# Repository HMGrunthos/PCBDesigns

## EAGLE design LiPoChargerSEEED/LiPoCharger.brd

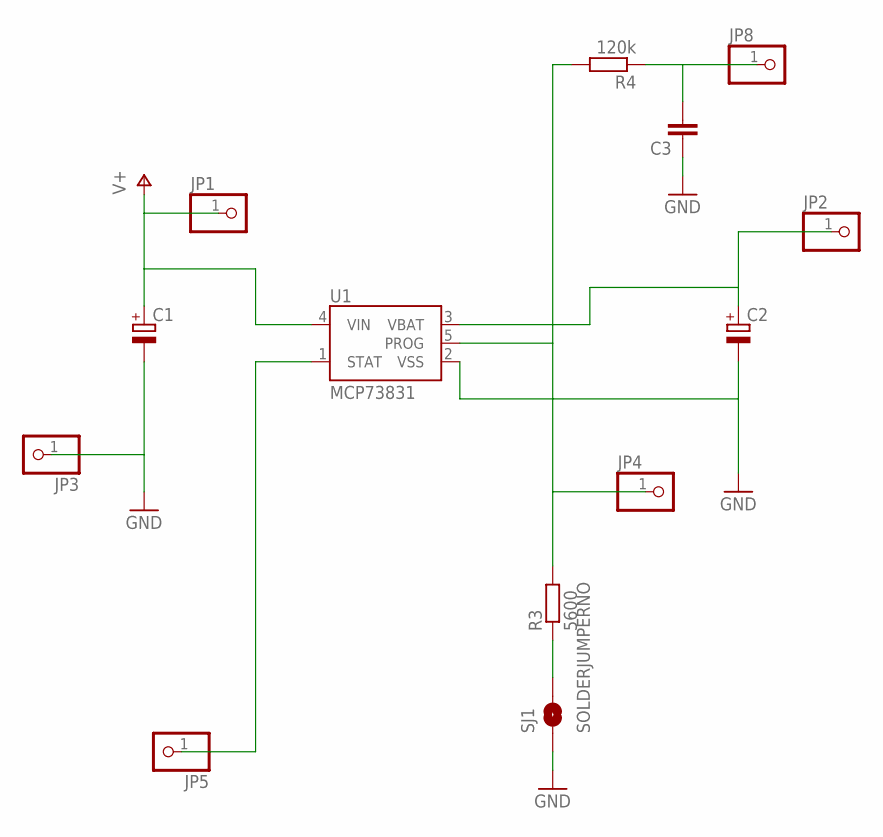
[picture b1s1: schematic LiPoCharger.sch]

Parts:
C1, C2: CPOL-EUE2.5-6; E2,5-6
C3: C-EUC1206; C1206
JP1, JP2, JP3, JP4, JP5, JP8: PINHD-1X1; 1X01
R3: 5600; R0402
R4: 120k; R0402
SJ1: SOLDERJUMPERNO; SJ_2S-NO
U1: MCP73831; SOT23-5

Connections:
GND: C1.-, C2.-, C3.1, JP3.1, SJ1.1, U1.2 (VSS)
unnamed: JP5.1, U1.1 (STAT)
unnamed: JP4.1, R3.2, R4.2, U1.5 (PROG)
unnamed: C3.2, JP8.1, R4.1
unnamed: R3.1, SJ1.2
V+: C1.+, JP1.1, U1.4 (VIN)
VBATT: C2.+, JP2.1, U1.3 (VBAT)

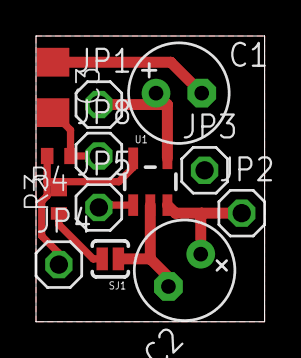
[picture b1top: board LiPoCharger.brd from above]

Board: 2 copper layers, 12.7 x 15.9 mm, 13 parts (0 on the bottom side), 7 nets.

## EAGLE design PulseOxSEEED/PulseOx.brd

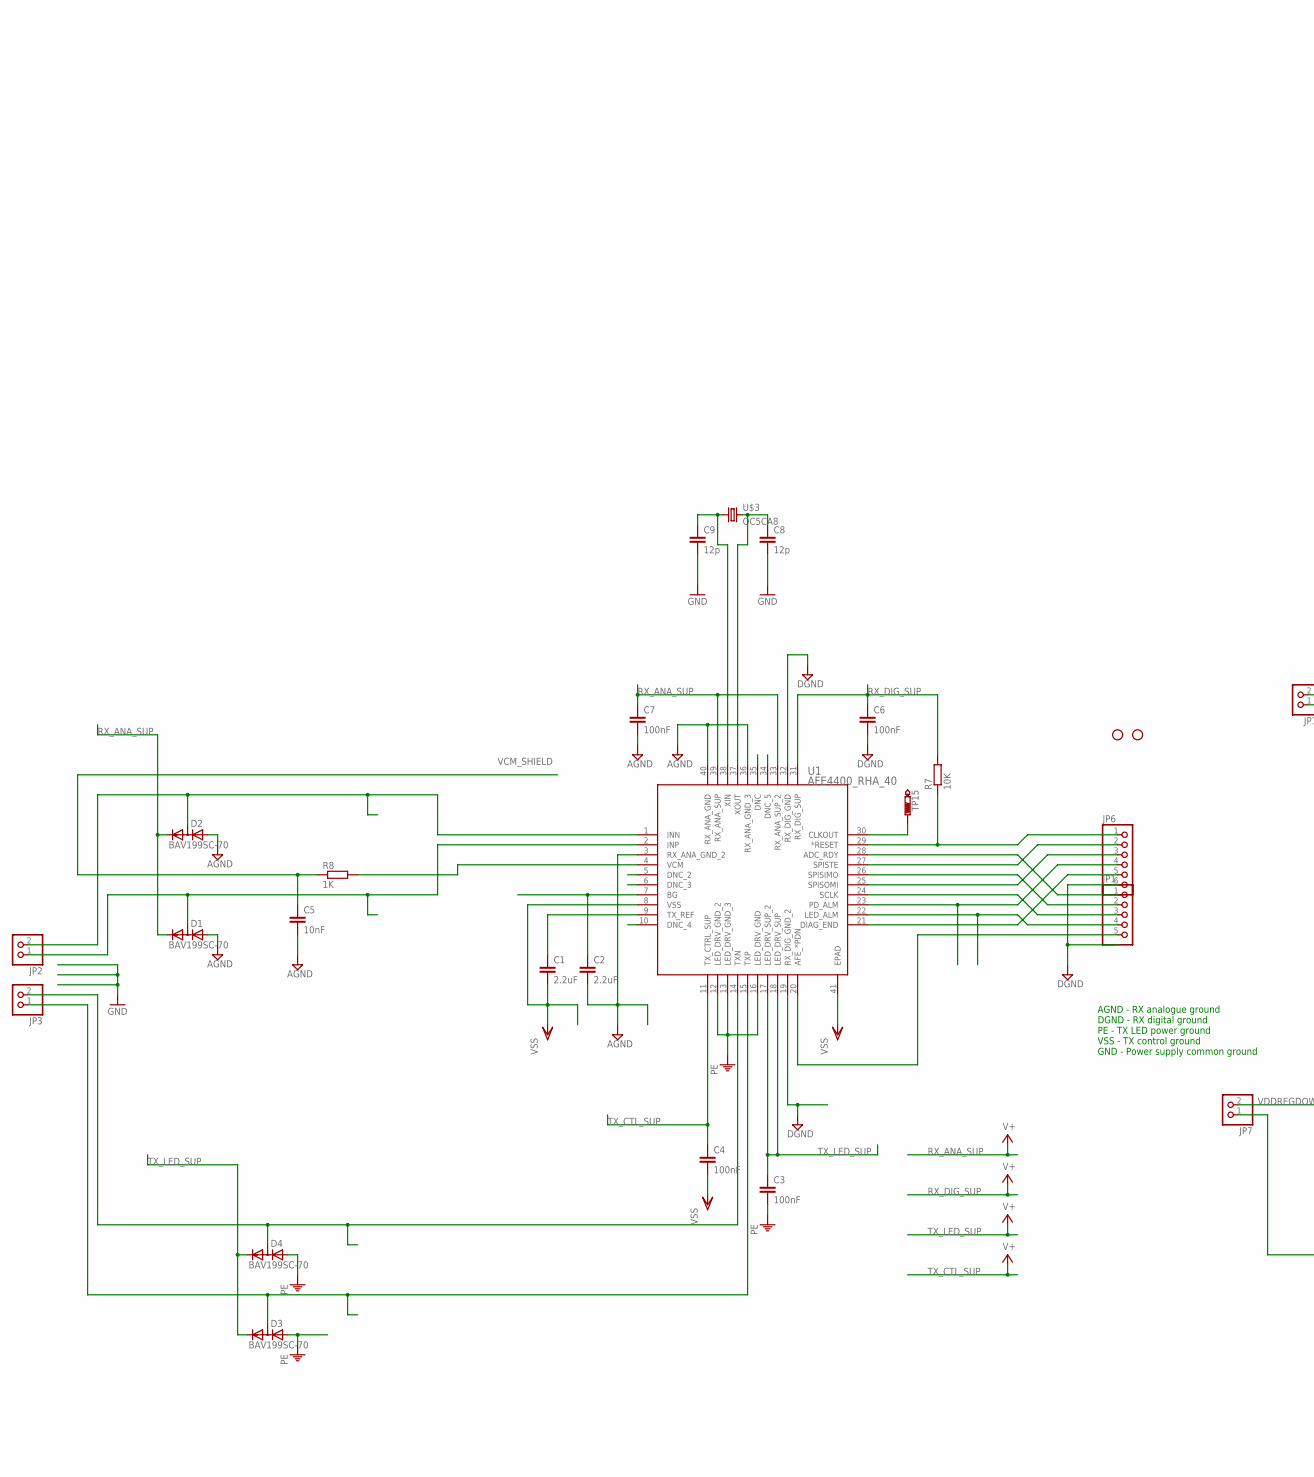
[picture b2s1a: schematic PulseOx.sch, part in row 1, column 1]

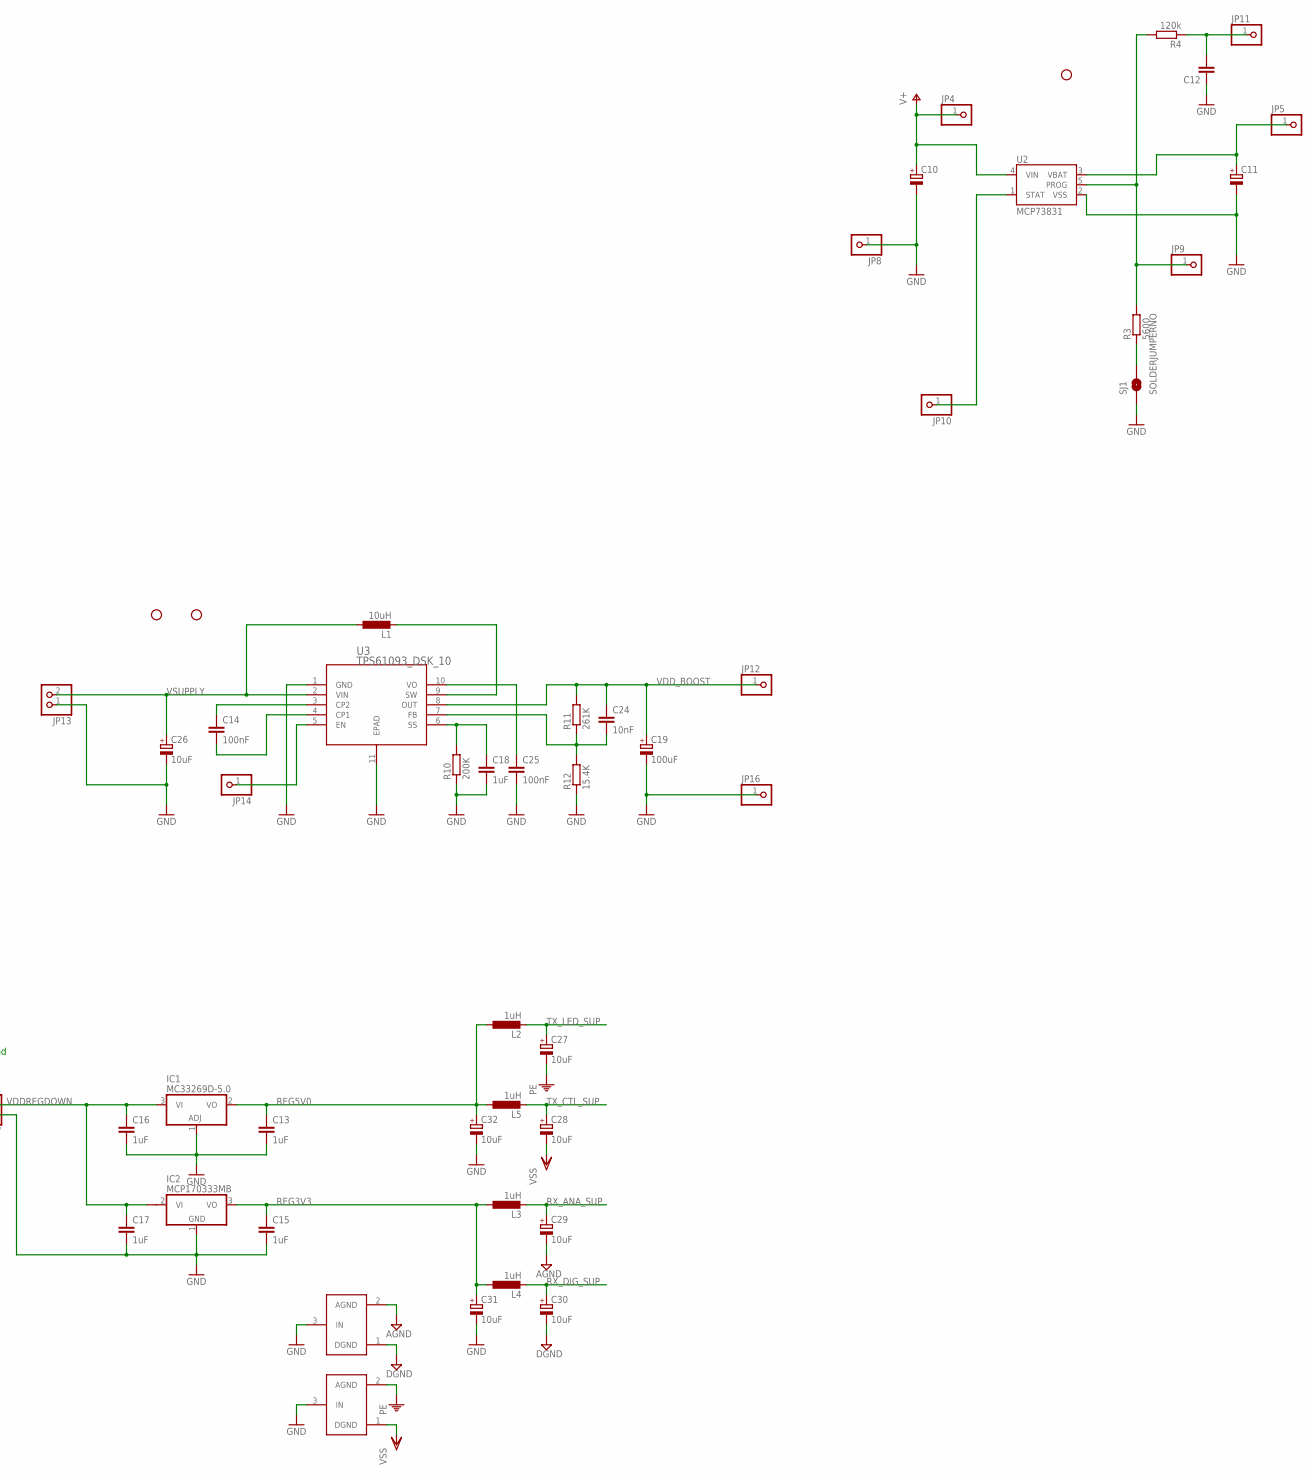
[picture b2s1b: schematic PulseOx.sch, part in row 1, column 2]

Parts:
C1, C2: 2.2uF; C1206K
C3, C4, C6, C7, C14, C25: 100nF; C1206K
C5, C24: 10nF; C0603K
C8, C9: 12p; C0603K
C10, C11: CPOL-EUE2.5-6; E2,5-6
C12: C-EUC1206; C1206
C13, C15, C16, C17, C18: 1uF; C1206K
C19: 100uF; TT2D5
C26, C27, C28, C29, C30, C31, C32: 10uF; TT2D5
D1, D2, D3, D4: BAV199SC-70; SC-70
IC1: MC33269D-5.0; DPACK
IC2: MCP170333MB; SOT89
JP1: PINHD-1X5; 1X05
JP2, JP3, JP7, JP13: PINHD-1X2; 1X02
JP4, JP5, JP8, JP9, JP10, JP11, JP12, JP14, JP16: PINHD-1X1; 1X01
JP6: PINHD-1X6; 1X06
L1: 10uH; D53LC
L2, L3, L4, L5: 1uH; L1515
R3: 5600; R0402
R4: 120k; R0402
R7: 10K; R0805
R8: 1K; R0402
R10: 200K; R0603
R11: 261K; R0603
R12: 15.4K; R0603
SJ1: SOLDERJUMPERNO; SJ_2S-NO
STANDOFF1, STANDOFF2, STANDOFF3, STANDOFF4, STANDOFF5: STAND-OFF
TP15: PTR1TP12R; TP12R
U1: AFE4400_RHA_40; RHA40_4P15X4P15
U2: MCP73831; SOT23-5
U3: TPS61093_DSK_10; DSK10_2X1P2
U$1, U$2: GND_CONNECT
U$3: QC5CA8; QC5CA

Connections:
AFE_PDN: JP1.5, U1.20 (AFE_*PDN)
AGND: C2.2, C5.2, C7.2, C29.-, D1.2 (A), D2.2 (A), U1.3 (RX_ANA_GND_2), U1.36 (RX_ANA_GND_3), U1.40 (RX_ANA_GND), U$1.2 (AGND)
DGND: C6.2, C30.-, JP6.6, U1.19 (RX_DIG_GND_2), U1.32 (RX_DIG_GND), U$1.1 (DGND)
GND: C8.2, C9.2, C13.2, C15.2, C16.2, C17.2, C31.-, C32.-, IC1.1 (ADJ), IC2.1 (GND), JP7.1, U$1.3 (IN), U$2.3 (IN)
GND1: C10.-, C11.-, C12.1, JP8.1, SJ1.1, U2.2 (VSS)
GND2: C18.2, C19.-, C25.2, C26.-, JP13.1, JP16.1, R10.1, R12.1, U3.1 (GND), U3.11 (EPAD)
INN: D2.3 (AC), JP2.2, U1.1 (INN)
INP: D1.3 (AC), JP2.1, U1.2 (INP)
unnamed: C2.1, U1.7 (BG)
unnamed: TP15.TP, U1.30 (CLKOUT)
unnamed: JP6.1, R7.1, U1.29 (*RESET)
unnamed: JP1.1, U1.28 (ADC_RDY)
unnamed: JP6.2, U1.27 (SPISTE)
unnamed: JP1.2, U1.26 (SPISIMO)
unnamed: JP6.3, U1.25 (SPISOMI)
unnamed: JP1.3, U1.24 (SCLK)
unnamed: JP6.4, U1.23 (PD_ALM)
unnamed: JP1.4, U1.22 (LED_ALM)
unnamed: JP6.5, U1.21 (DIAG_END)
unnamed: C1.1, U1.9 (TX_REF)
unnamed: JP10.1, U2.1 (STAT)
unnamed: JP9.1, R3.2, R4.2, U2.5 (PROG)
unnamed: C12.2, JP11.1, R4.1
unnamed: R3.1, SJ1.2
unnamed: C14.2, U3.4 (CP1)
unnamed: C14.1, U3.3 (CP2)
unnamed: L1.P$2 (2), U3.9 (SW)
unnamed: C24.2, R11.1, R12.2, U3.7 (FB)
unnamed: C18.1, R10.2, U3.6 (SS)
unnamed: R8.2, U1.4 (VCM)
unnamed: C25.1, U3.10 (VO)
unnamed: JP14.1, U3.5 (EN)
unnamed: C9.1, U1.38 (XIN), U$3.1
unnamed: C8.1, U1.37 (XOUT), U$3.3 (2)
PE: C3.2, C27.-, D3.2 (A), D4.2 (A), U1.12 (LED_DRV_GND_2), U1.13 (LED_DRV_GND_3), U1.16 (LED_DRV_GND), U$2.2 (AGND)
REG3V3: C15.1, C31.+, IC2.3 (VO), L3.1, L4.1
REG5V0: C13.1, C32.+, IC1.2 (VO), L2.1, L5.1
RX_ANA_SUP: C7.1, C29.+, D1.1 (C), D2.1 (C), L3.2, U1.33 (RX_ANA_SUP_2), U1.39 (RX_ANA_SUP)
RX_DIG_SUP: C6.1, C30.+, L4.2, R7.2, U1.31 (RX_DIG_SUP)
TXN: D4.3 (AC), JP3.2, U1.14 (TXN)
TXP: D3.3 (AC), JP3.1, U1.15 (TXP)
TX_CTL_SUP: C4.1, C28.+, L5.2, U1.11 (TX_CTRL_SUP)
TX_LED_SUP: C3.1, C27.+, D3.1 (C), D4.1 (C), L2.2, U1.17 (LED_DRV_SUP_2), U1.18 (LED_DRV_SUP)
V+: C10.+, JP4.1, U2.4 (VIN)
VBATT: C11.+, JP5.1, U2.3 (VBAT)
VCM_SHIELD: C5.1, R8.1
VDDREGDOWN: C16.1, C17.1, IC1.3 (VI), IC2.2@1 (VI1), JP7.2
VDD_BOOST: C19.+, C24.1, JP12.1, R11.2, U3.8 (OUT)
VSS: C1.2, C4.2, C28.-, U1.8 (VSS), U1.41 (EPAD), U$2.1 (DGND)
VSUPPLY: C26.+, JP13.2, L1.P$1 (1), U3.2 (VIN)

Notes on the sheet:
AGND - RX analogue ground DGND - RX digital ground PE - TX LED power ground VSS - TX control ground GND - Power supply common ground

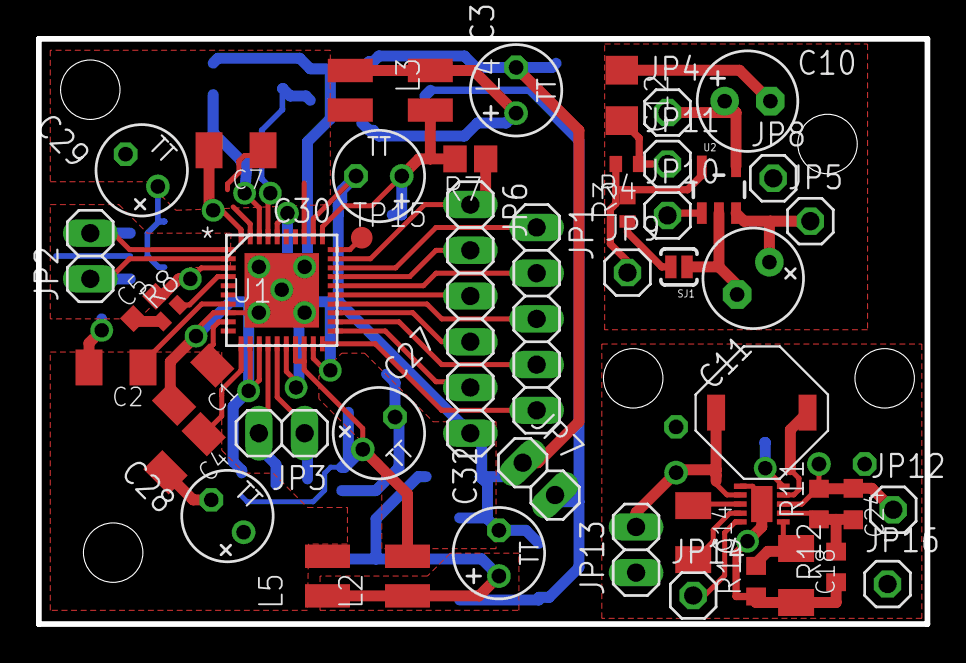
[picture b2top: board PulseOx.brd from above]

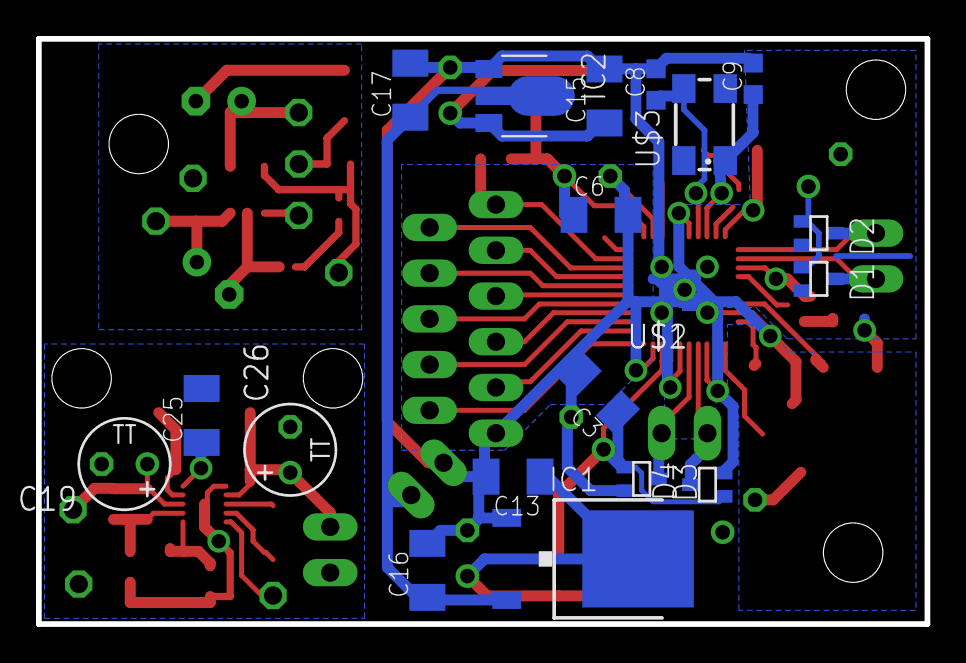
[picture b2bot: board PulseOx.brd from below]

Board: 2 copper layers, 49.4 x 32.5 mm, 74 parts (20 on the bottom side), 50 nets.

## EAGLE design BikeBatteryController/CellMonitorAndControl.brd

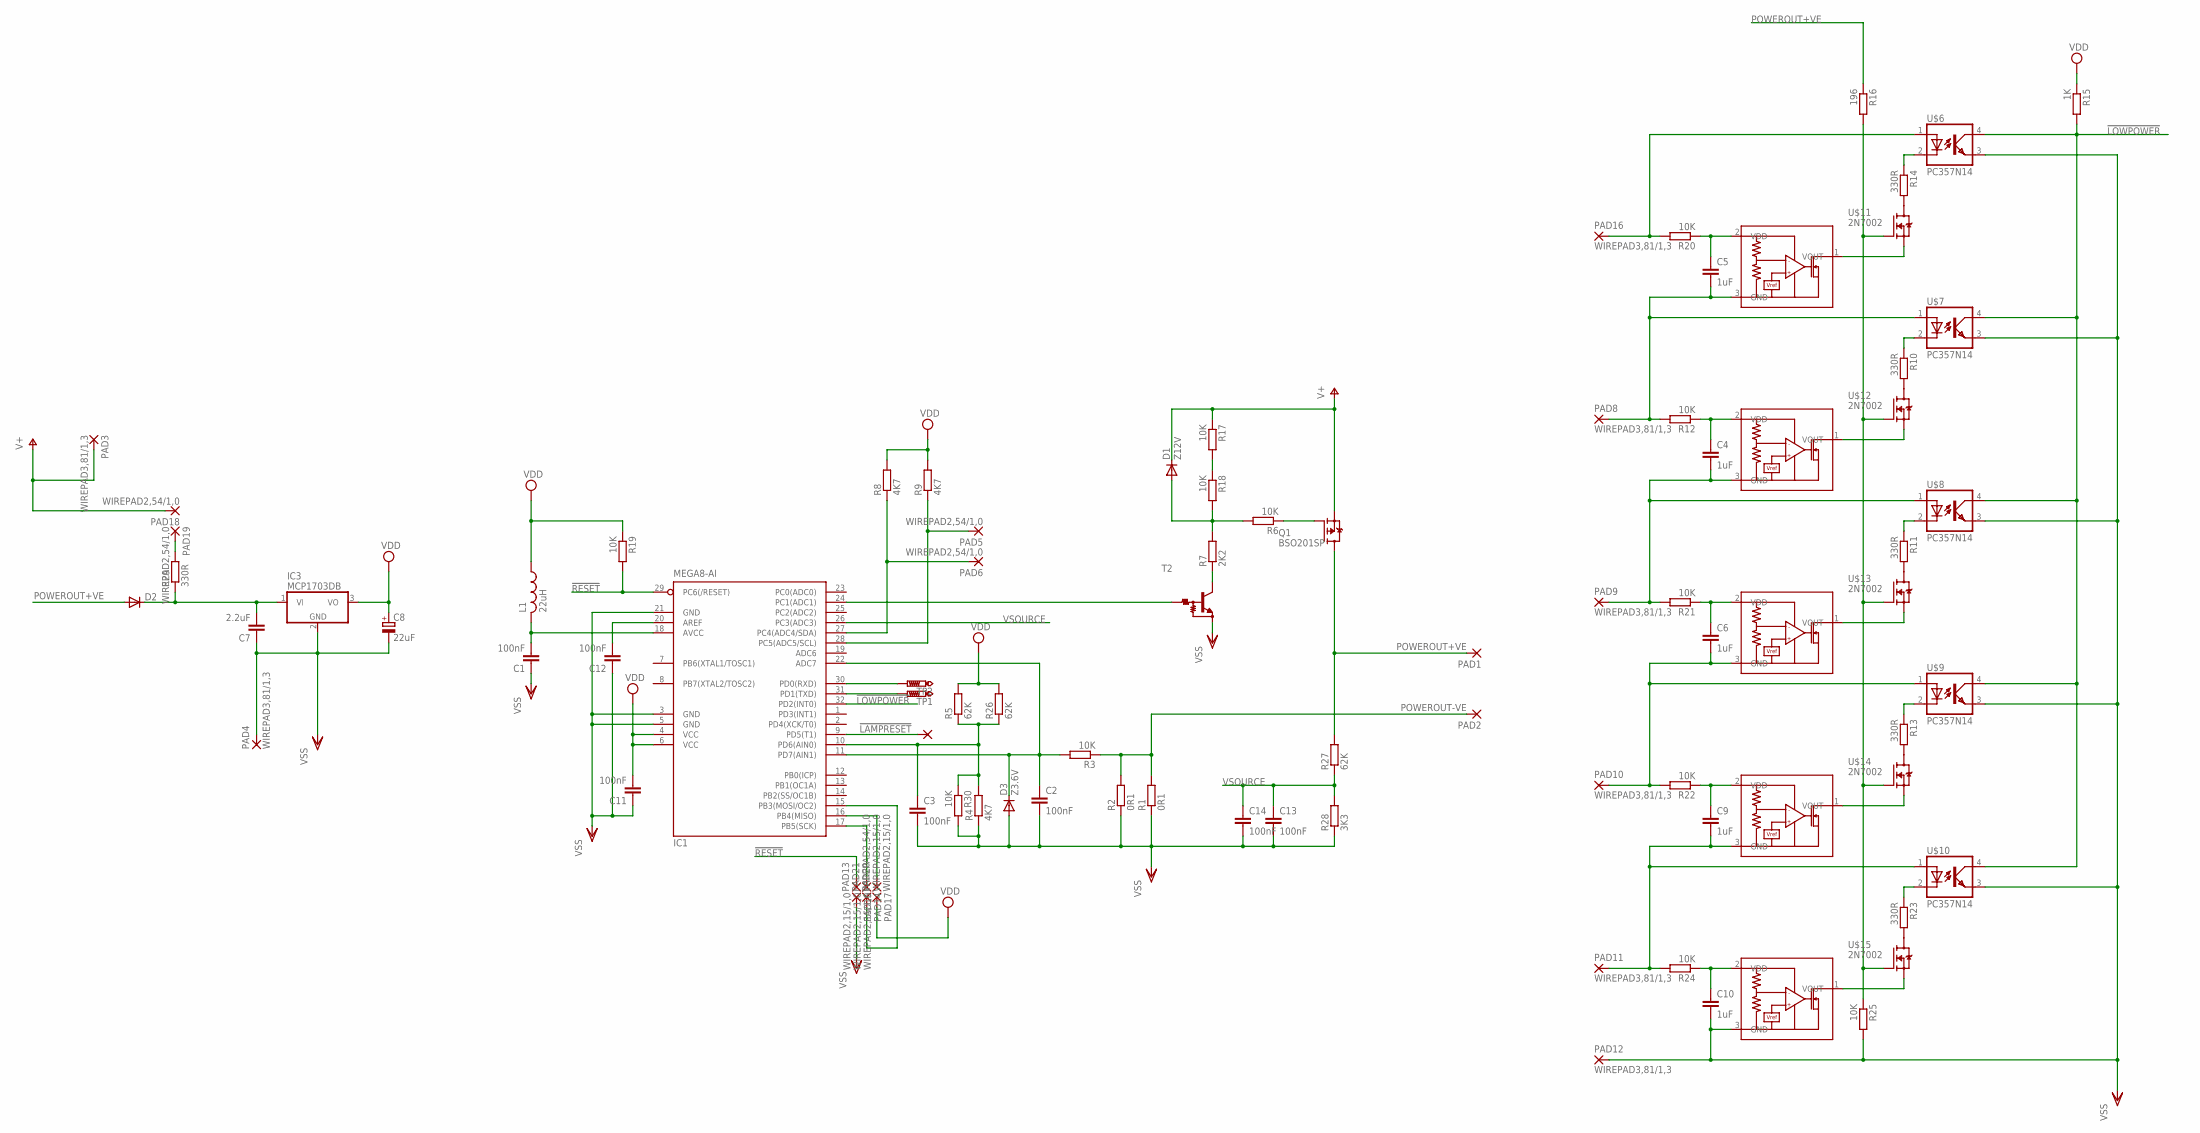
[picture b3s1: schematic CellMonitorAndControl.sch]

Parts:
C1, C2, C3, C11, C12, C13, C14: 100nF; C1206
C4, C5, C6, C9, C10: 1uF; C1206
C7: 2.2uF; C1206
C8: 22uF; B/3528-21R
D1: Z12V; SOD323-W
D2: DIODE-SOD123; SOD123
D3: Z3.6V; SOD323-R
IC1: MEGA8-AI; TQFP32-08
IC3: MCP1703DB; SOT223
L1: 22uH; ELL6SH
PAD1, PAD2, PAD3, PAD4, PAD8, PAD9, PAD10, PAD11, PAD12, PAD16: WIREPAD3,81/1,3; 3,81/1,3
PAD5, PAD6, PAD7, PAD13, PAD18, PAD19: WIREPAD2,54/1,0; 2,54/1,0
PAD14, PAD15, PAD17, PAD20, PAD21: WIREPAD2,15/1,0; 2,15/1,0
Q1: BSO201SP; SO-8
R1, R2: 0R1; R2512
R3, R6, R12, R17, R18, R19, R20, R21, R22, R24, R25, R30: 10K; R0805
R4, R8, R9: 4K7; R0402
R5, R26, R27: 62K; R0402
R7: 2K2; R0402
R10, R11, R13, R14, R23, R29: 330R; R0402
R15: 1K; R0402
R16: 196; R0805
R28: 3K3; R0603
T2: -NPN_DRIVER-; SOT23
TP1, TP2: PTR1B1,27; B1,27
U$1, U$2, U$3, U$4, U$5: BU48XXG; SOT95P280X125-5N
U$6, U$7, U$8, U$9, U$10: PC357N14; MINI-FLAT-4-DS
U$11, U$12, U$13, U$14, U$15: 2N7002; SOT23

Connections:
!LAMPRESET: IC1.9 (PD5(T1)), PAD7.1
!LOWPOWER: IC1.32 (PD2(INT0)), R15.2, U$6.4 (COL), U$7.4 (COL), U$8.4 (COL), U$9.4 (COL), U$10.4 (COL)
!RESET: IC1.29 (PC6(/RESET)), PAD13.1, R19.2
unnamed: Q1.4 (G), R6.1
unnamed: R14.2, U$11.3 (D)
unnamed: C2.1, D3.C, IC1.11 (PD7(AIN1)), IC1.22 (ADC7), R3.2
unnamed: D1.A, R6.2, R7.2, R18.2
unnamed: R10.2, U$12.3 (D)
unnamed: R7.1, T2.3 (C)
unnamed: C5.1, R20.1, U$1.2 (VDD)
unnamed: R17.2, R18.1
unnamed: IC1.24 (PC1(ADC1)), T2.1 (B)
unnamed: IC1.27 (PC4(ADC4/SDA)), PAD6.1, R8.1
unnamed: IC1.28 (PC5(ADC5/SCL)), PAD5.1, R9.1
unnamed: R11.2, U$13.3 (D)
unnamed: U$1.1 (VOUT), U$11.2 (S)
unnamed: R14.1, U$6.2 (C)
unnamed: C3.1, IC1.10 (PD6(AIN0)), R4.2, R5.1, R26.1, R30.1
unnamed: C5.2, PAD8.1, R12.2, U$1.3 (GND), U$7.1 (A)
unnamed: R13.2, U$14.3 (D)
unnamed: U$2.1 (VOUT), U$12.2 (S)
unnamed: R10.1, U$7.2 (C)
unnamed: R23.2, U$15.3 (D)
unnamed: C4.1, R12.1, U$2.2 (VDD)
unnamed: C4.2, PAD9.1, R21.2, U$2.3 (GND), U$8.1 (A)
unnamed: C1.2, IC1.18 (AVCC), L1.2
unnamed: C12.2, IC1.20 (AREF)
unnamed: U$3.1 (VOUT), U$13.2 (S)
unnamed: R11.1, U$8.2 (C)
unnamed: IC1.16 (PB4(MISO)), PAD20.1
unnamed: C6.1, R21.1, U$3.2 (VDD)
unnamed: IC1.17 (PB5(SCK)), PAD21.1
unnamed: C6.2, PAD10.1, R22.2, U$3.3 (GND), U$9.1 (A)
unnamed: IC1.15 (PB3(MOSI/OC2)), PAD14.1
unnamed: U$4.1 (VOUT), U$14.2 (S)
unnamed: R13.1, U$9.2 (C)
unnamed: PAD16.1, R20.2, U$6.1 (A)
unnamed: PAD19.1, R29.2
unnamed: C9.1, R22.1, U$4.2 (VDD)
unnamed: IC1.30 (PD0(RXD)), TP2.TP
unnamed: C9.2, PAD11.1, R24.2, U$4.3 (GND), U$10.1 (A)
unnamed: IC1.31 (PD1(TXD)), TP1.TP
unnamed: U$5.1 (VOUT), U$15.2 (S)
unnamed: R23.1, U$10.2 (C)
unnamed: C10.1, R24.1, U$5.2 (VDD)
unnamed: R16.2, R25.1, U$11.1 (G), U$12.1 (G), U$13.1 (G), U$14.1 (G), U$15.1 (G)
POWEROUT+VE: D2.A, PAD1.1, Q1.5 (D), Q1.6 (D), Q1.7 (D), Q1.8 (D), R16.1, R27.2
POWEROUT-VE: PAD2.1, R1.2, R2.2, R3.1
V+: D1.C, PAD3.1, PAD18.1, Q1.1 (S), Q1.2 (S), Q1.3 (S), R17.1
VDD: C8.+, C11.2, IC1.4 (VCC), IC1.6 (VCC), IC3.3 (VO), L1.1, PAD17.1, R5.2, R8.2, R9.2, R15.1, R19.1, R26.2
VIN: C7.2, D2.C, IC3.1 (VI), R29.1
VSOURCE: C13.1, C14.1, IC1.26 (PC3(ADC3)), R27.1, R28.2
VSS: C1.1, C2.2, C3.2, C7.1, C8.-, C10.2, C11.1, C12.1, C13.2, C14.2, D3.A, IC1.3 (GND), IC1.5 (GND), IC1.21 (GND), IC3.2 (GND), PAD4.1, PAD12.1, PAD15.1, R1.1, R2.1, R4.1, R25.2, R28.1, R30.2, T2.2 (E), U$5.3 (GND), U$6.3 (EMIT), U$7.3 (EMIT), U$8.3 (EMIT), U$9.3 (EMIT), U$10.3 (EMIT)

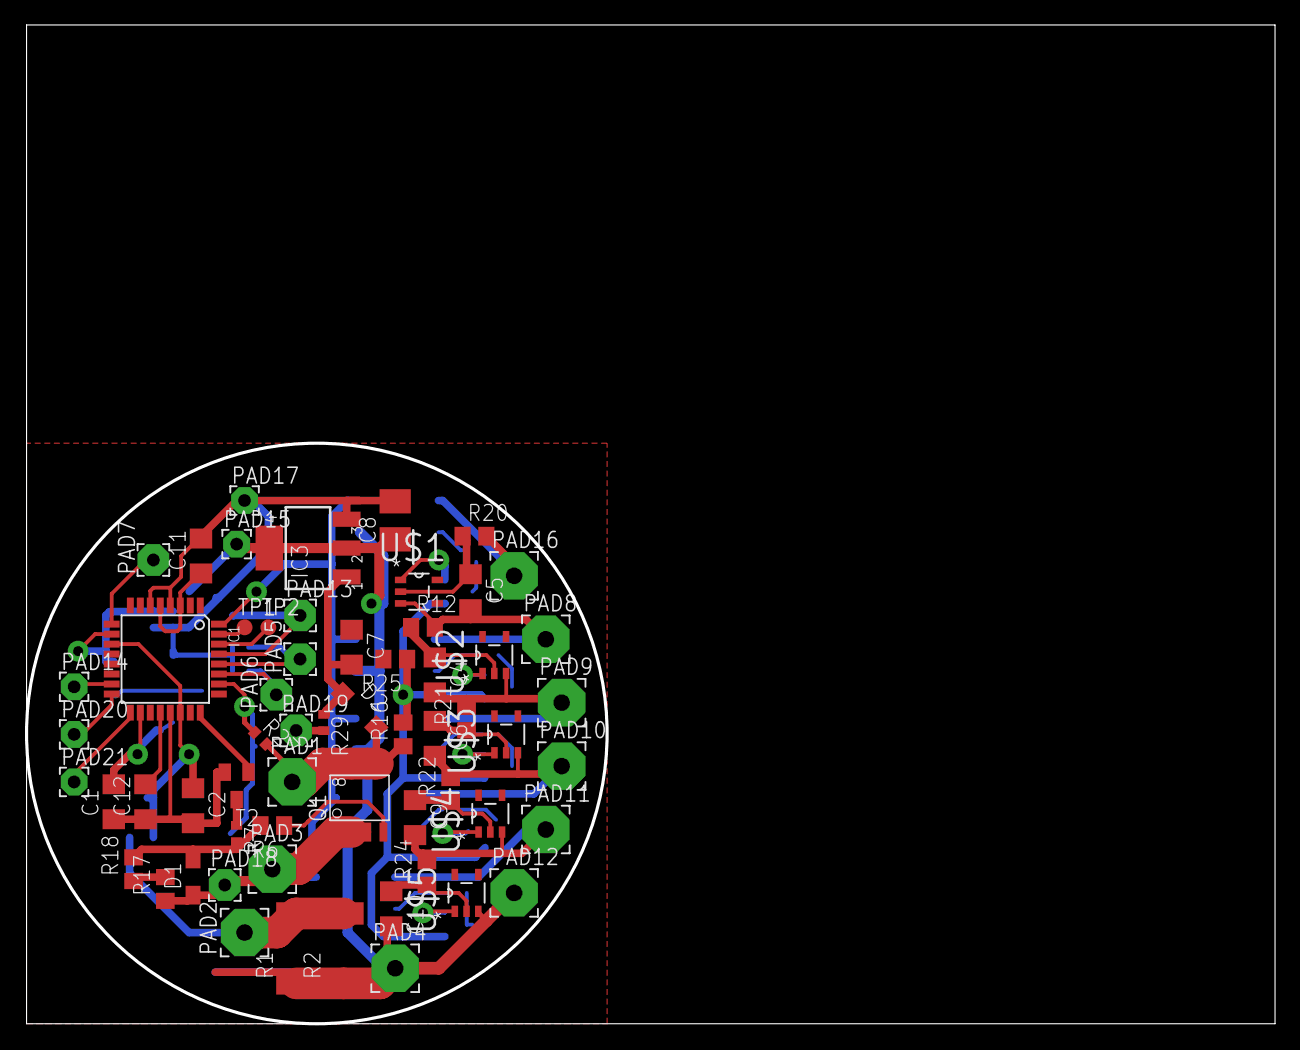
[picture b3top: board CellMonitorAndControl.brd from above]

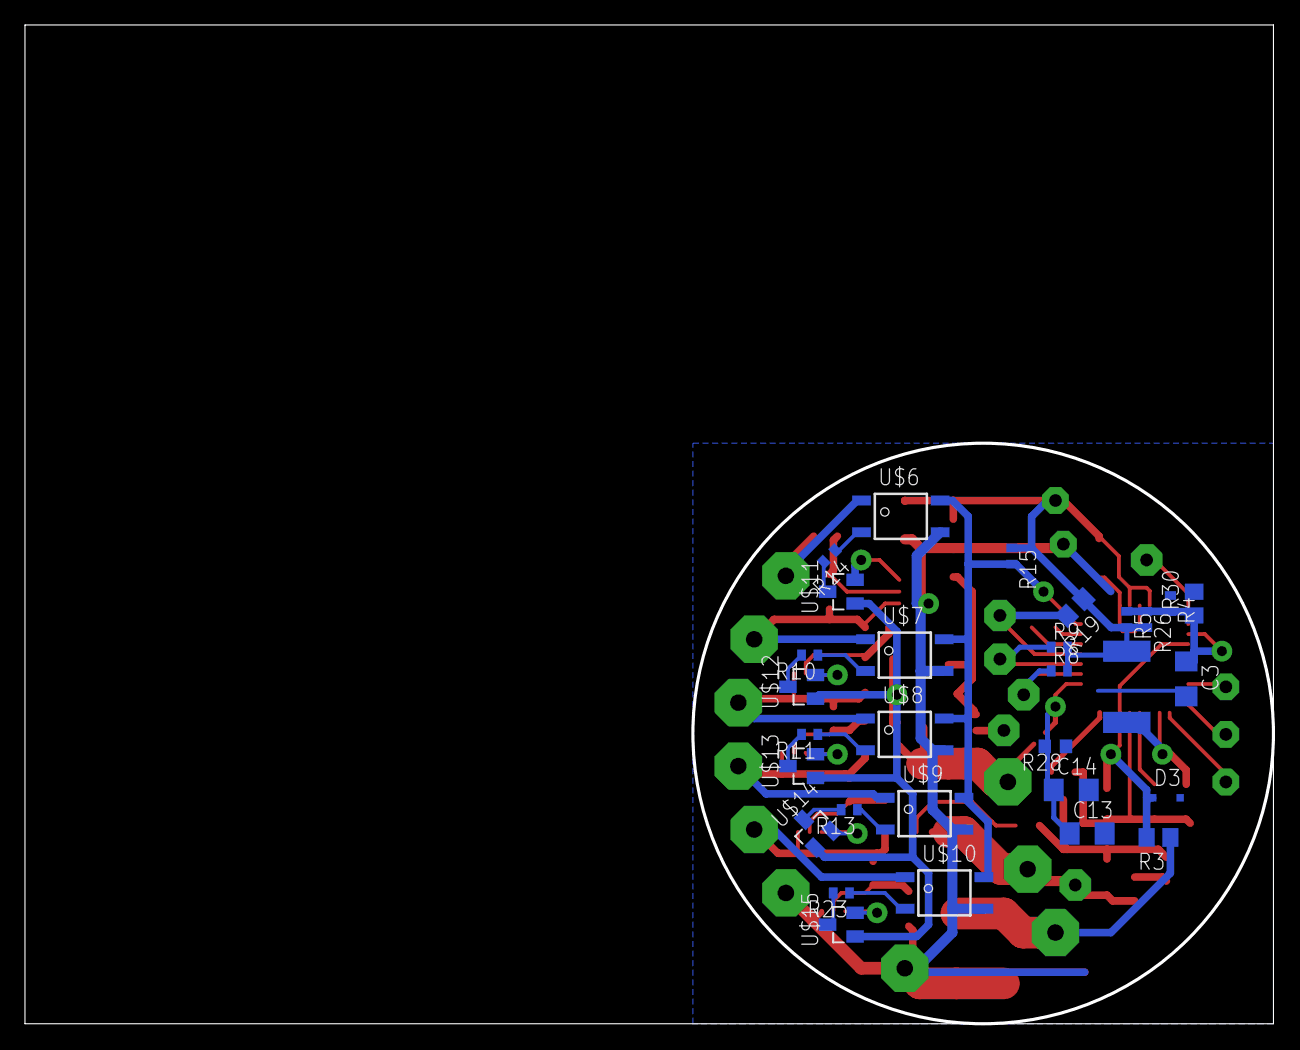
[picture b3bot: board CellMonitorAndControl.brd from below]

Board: 2 copper layers, 99.9 x 79.9 mm, 90 parts (30 on the bottom side), 53 nets.

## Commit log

2018-05-12 Initial check in

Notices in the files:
parts and their libraries:
SparkFun-Passives: Licensing: Creative Commons ShareAlike 4.0 International - https://creativecommons.org/licenses/by-sa/4.0
